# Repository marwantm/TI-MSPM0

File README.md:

# TI MSPM0 Development Board
 
A 2-layer TI MSPM0 development board, designed in KiCad by following Phil's Lab's tutorial — this time spending less effort on replicating the steps and more on understanding the engineering decisions behind each one.

## Overview
 
This board is built around the **MSPM0G3507SPTR**, an Arm Cortex-M0+ MCU from Texas Instruments. It includes USB-C power/data via a USB-UART converter, an SWD programming header, an onboard 3.3V LDO regulator, and an onboard accelerometer — a compact general-purpose MSPM0 development platform.
 
| | |
|---|---|
| **MCU** | MSPM0G3507SPTR (Arm Cortex-M0+) |
| **Peripherals** | Onboard accelerometer (I2C) |
| **Connectivity** | USB-C, USB-to-UART bridge |
| **PCB** | 2-layer |
| **Programming** | SWD header |
| **Power** | USB-C (5V → 3.3V via onboard LDO) |
| **Design Tool** | KiCad 9 |
 
## What I Learned
 
Compared to my first PCB project, I spent less time simply following the tutorial and more time understanding the engineering decisions behind each step:
 
- Creating custom schematic symbols
- Multilayer PCB concepts and layer stack-ups
- The role of signal, power, and ground layers
- PCB manufacturing basics
- Component placement strategies
- A professional PCB layout workflow
Each project is helping me strengthen both my PCB design and embedded systems fundamentals, moving closer to making these design decisions independently.
 
## Gallery
 
| Schematic | PCB Top | PCB Bottom |
|---|---|---|
|  |  |  |
 
| 3D Front | 3D Back |
|---|---|
|  |  |
 
## Repository Structure
 
```
TI-MSPM0/
├── README.md
├── Images/              # Renders and layer screenshots
├── Hardware/            # Manufacturing-ready outputs
│   ├── TI MSPM0_Schematic.pdf
│   ├── TI MSPM0_PCB.pdf
│   ├── BOM.csv
│   └── Gerbers.zip
└── Source Files/        # Full KiCad project (editable source)
```
 
## Credit
 
Built by following [Phil's Lab](https://www.youtube.com/@PhilsLab)'s TI MSPM0 development board tutorial. This project is a learning exercise, not an original design — full credit for the schematic architecture and design decisions goes to Phil's Lab's tutorial series.
 
## Author
 
**Marwan Tamer**
Electrical Power Engineering student, building toward Embedded Systems Engineering
[LinkedIn](https://www.linkedin.com/in/-marwan-tamer)

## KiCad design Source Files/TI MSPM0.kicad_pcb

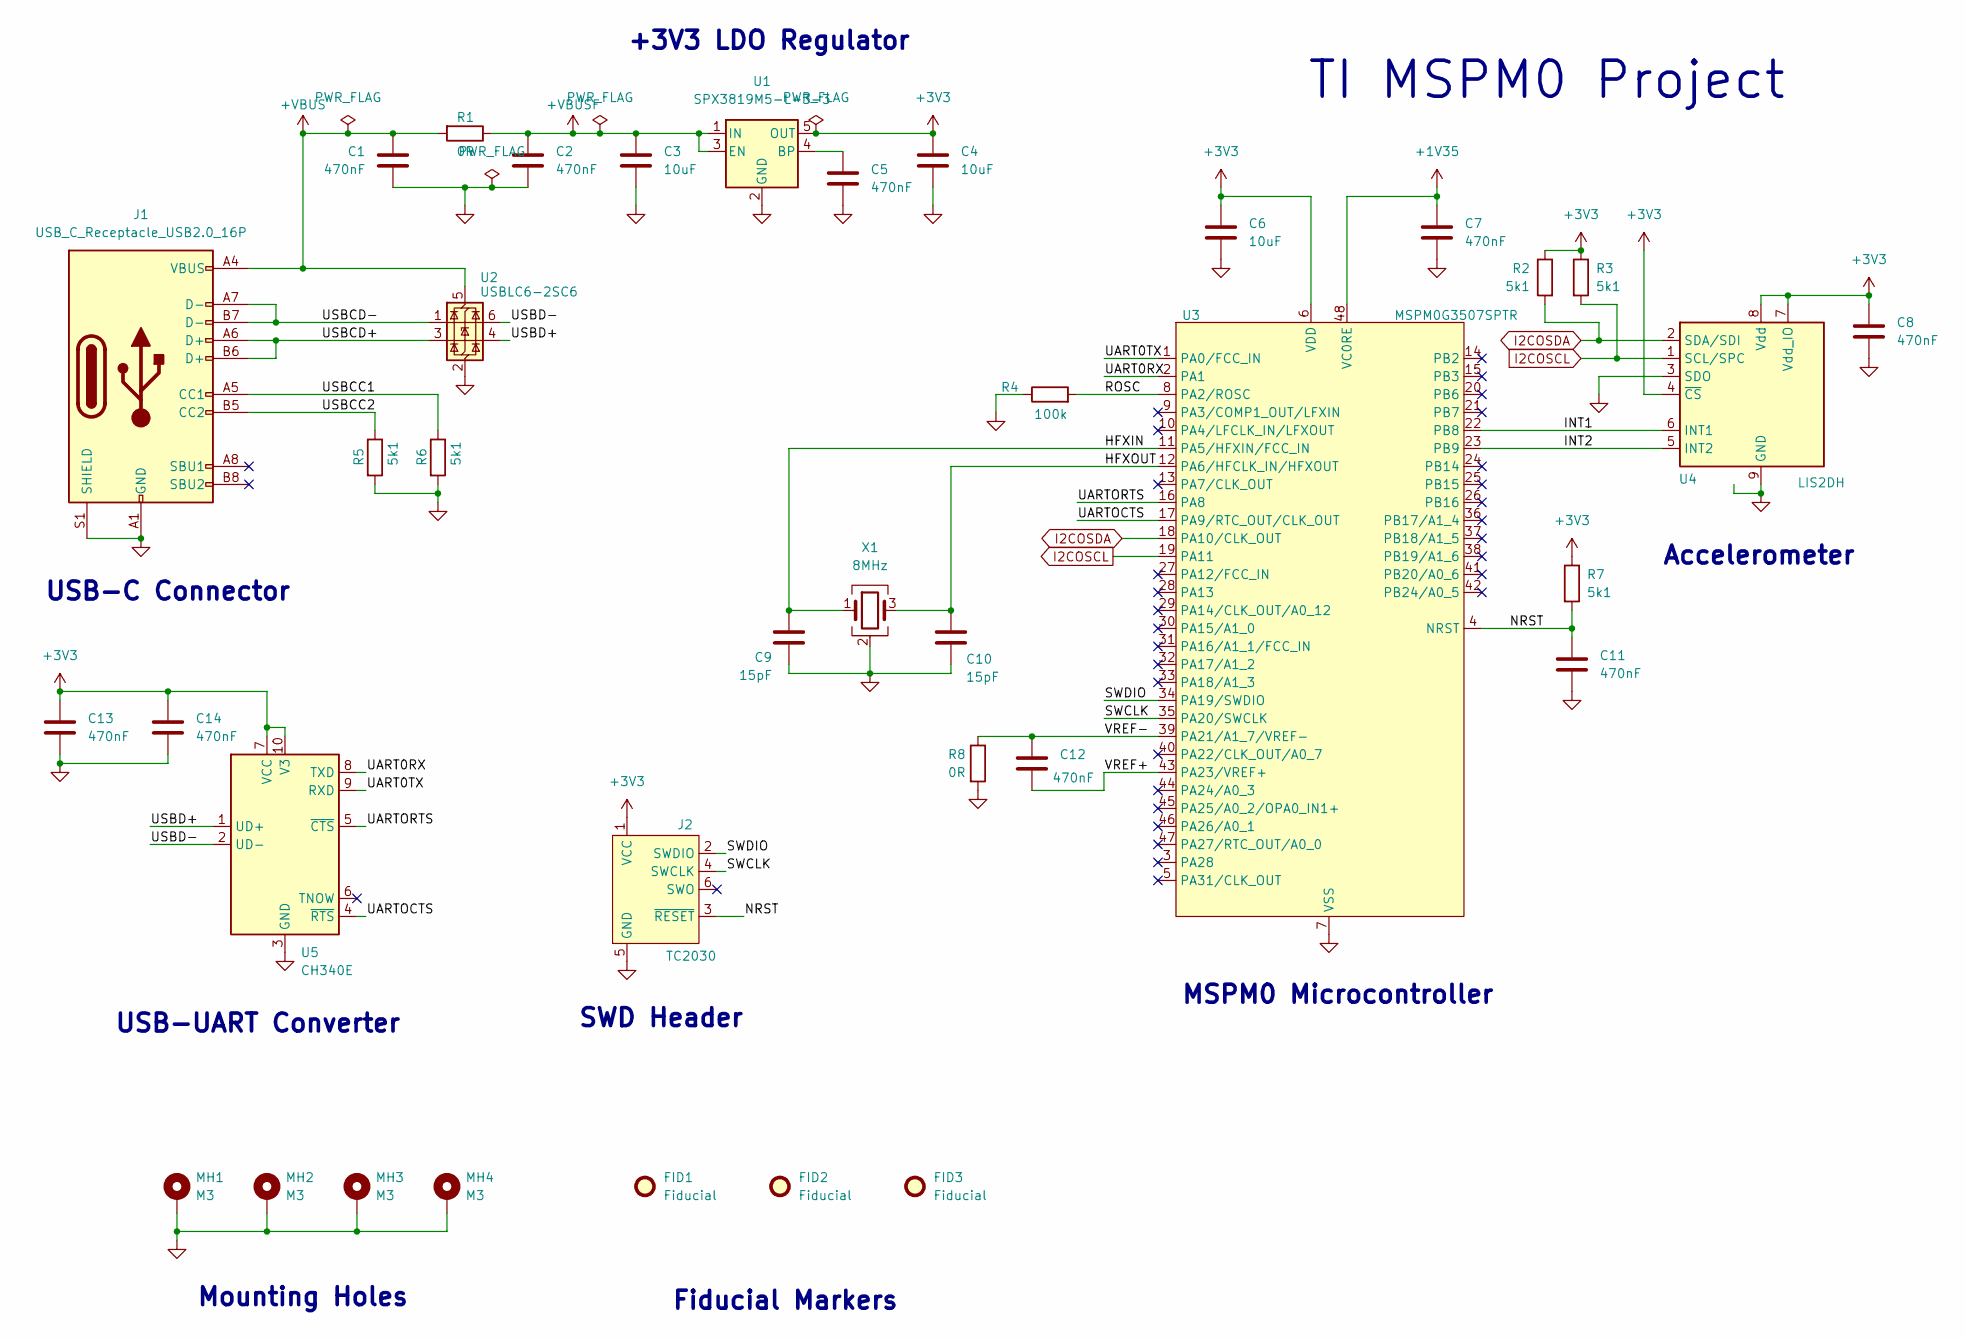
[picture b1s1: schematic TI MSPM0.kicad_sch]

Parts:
C1, C2, C5, C7, C8, C11, C12, C13, C14: 470nF; C_0603_1608Metric
C3, C4, C6: 10uF; C_0805_2012Metric
C9, C10: 15pF; C_0603_1608Metric
FID1, FID2, FID3: Fiducial; Fiducial_1mm_Mask2mm
J1: USB_C_Receptacle_USB2.0_16P; USB_C_Receptacle_GCT_USB4105-xx-A_16P_TopMnt_Horizontal
J2: TC2030; Tag-Connect_TC2030-IDC-FP_2x03_P1.27mm_Vertical
MH1, MH2, MH3, MH4: M3; MountingHole_3.2mm_M3_Pad_Via
R1, R8: 0R; R_0603_1608Metric
R2, R3, R5, R6, R7: 5k1; R_0603_1608Metric
R4: 100k; R_0603_1608Metric
U1: SPX3819M5-L-3-3; SOT-23-5
U2: USBLC6-2SC6; SOT-23-6
U3: MSPM0G3507SPTR; LQFP-48_7x7mm_P0.5mm
U4: LIS2DH; LGA-14_2x2mm_P0.35mm_LayoutBorder3x4y
U5: CH340E; MSOP-10_3x3mm_P0.5mm
X1: 8MHz; Crystal_SMD_3225-4Pin_3.2x2.5mm

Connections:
+1V35: C7.1, U3.48 (VC0RE)
+3V3: C4.1, C6.1, C8.1, C13.1, C14.1, J2.1 (VCC), R2.1, R3.1, R7.1, U1.5 (OUT), U3.6 (VDD), U4.4 (~CS), U4.7 (Vdd_IO), U4.8 (Vdd), U5.7 (VCC), U5.10 (V3)
+VBUS: C1.1, J1.A4 (VBUS), J1.A9 (VBUS), J1.B4 (VBUS), J1.B9 (VBUS), R1.2, U2.5 (VBUS)
+VBUSF: C2.1, C3.1, R1.1, U1.1 (IN), U1.3 (EN)
/HFXIN: C9.1, U3.11 (PA5/HFXIN/FCC_IN), X1.1
/HFXOUT: C10.1, U3.12 (PA6/HFCLK_IN/HFXOUT), X1.3
/INT1: U3.22 (PB8), U4.6 (INT1)
/INT2: U3.23 (PB9), U4.5 (INT2)
/NRST: C11.1, J2.3 (~RESET), R7.2, U3.4 (NRST)
/ROSC: R4.2, U3.8 (PA2/ROSC)
/SWCLK: J2.4 (SWCLK), U3.35 (PA20/SWCLK)
/SWDIO: J2.2 (SWDIO), U3.34 (PA19/SWDIO)
/UART0RX: U3.2 (PA1), U5.8 (TXD)
/UART0TX: U3.1 (PA0/FCC_IN), U5.9 (RXD)
/UARTOCTS: U3.17 (PA9/RTC_OUT/CLK_OUT), U5.4 (~RTS)
/UARTORTS: U3.16 (PA8), U5.5 (~CTS)
/USBCC1: J1.A5 (CC1), R6.1
/USBCC2: J1.B5 (CC2), R5.1
/USBCD+: J1.A6 (D+), J1.B6 (D+), U2.3 (I/O2)
/USBCD-: J1.A7 (D-), J1.B7 (D-), U2.1 (I/O1)
/USBD+: U2.4 (I/O2), U5.1 (UD+)
/USBD-: U2.6 (I/O1), U5.2 (UD-)
/VREF+: C12.2, U3.43 (PA23/VREF+)
/VREF-: C12.1, R8.1, U3.39 (PA21/A1_7/VREF-)
GND: C1.2, C2.2, C3.2, C4.2, C5.2, C6.2, C7.2, C8.2, C9.2, C10.2, C11.2, C13.2, C14.2, J1.A1 (GND), J1.A12 (GND), J1.B1 (GND), J1.B12 (GND), J1.S1 (SHIELD), J2.5 (GND), MH1.1, MH2.1, MH3.1, MH4.1, R4.1, R5.2, R6.2, R8.2, U1.2 (GND), U2.2 (GND), U3.7 (VSS), U4.3 (SDO), U4.9 (GND), U4.10 (GND), U4.11 (GND), U4.12 (GND), U4.13 (GND), U4.14 (GND), U5.3 (GND), X1.2 (G), X1.4 (G)
I2COSCL: R3.2, U3.19 (PA11), U4.1 (SCL/SPC)
I2COSDA: R2.2, U3.18 (PA10/CLK_OUT), U4.2 (SDA/SDI)
unnamed: C5.1, U1.4 (BP)

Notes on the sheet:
Fiducial Markers
TI MSPM0 Project
USB-UART Converter
Mounting Holes
Accelerometer
SWD Header
USB-C Connector
MSPM0 Microcontroller
+3V3 LDO Regulator

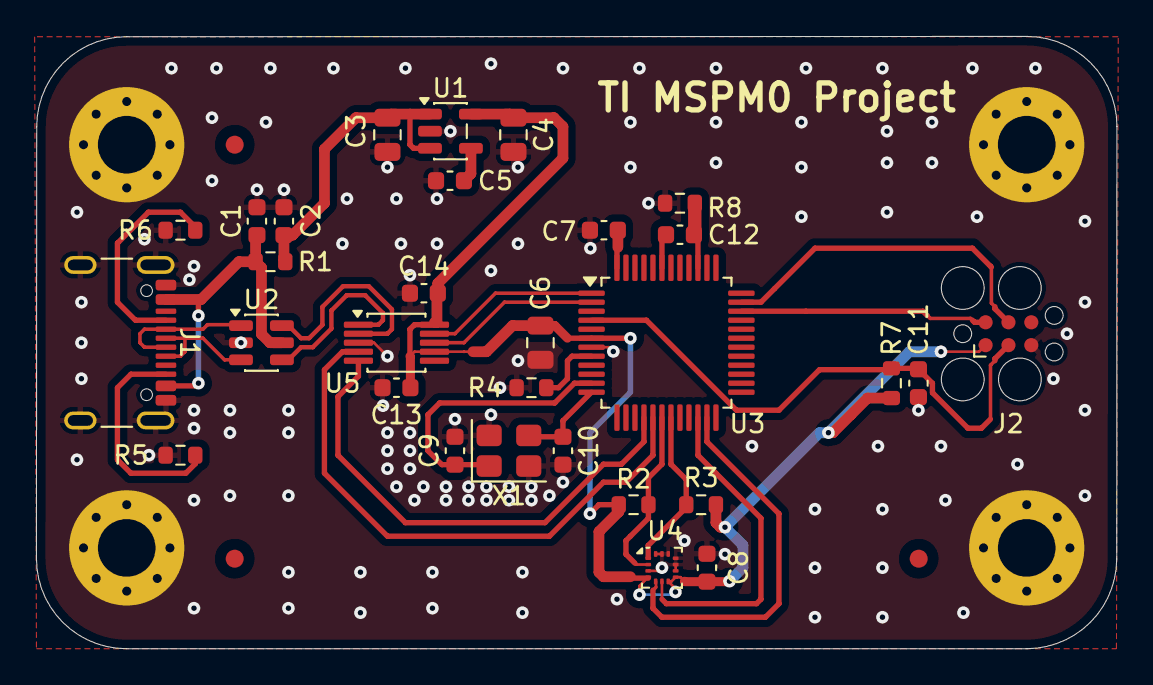
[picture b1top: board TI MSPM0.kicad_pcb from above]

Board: 2 copper layers, 60.0 x 34.0 mm, 37 parts (0 on the bottom side), 28 nets.

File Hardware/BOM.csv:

"Reference","Qty","Value","DNP","Exclude from BOM","Exclude from Board","Footprint","Datasheet"
"C1,C2,C5,C7,C8,C11,C12,C13,C14","9","470nF","","","","Capacitor_SMD:C_0603_1608Metric","~"
"C3,C4,C6","3","10uF","","","","Capacitor_SMD:C_0805_2012Metric","~"
"C9,C10","2","15pF","","","","Capacitor_SMD:C_0603_1608Metric","~"
"FID1,FID2,FID3","3","Fiducial","","Excluded from BOM","","Fiducial:Fiducial_1mm_Mask2mm","~"
"J1","1","USB_C_Receptacle_USB2.0_16P","","","","Connector_USB:USB_C_Receptacle_GCT_USB4105-xx-A_16P_TopMnt_Horizontal","https://www.usb.org/sites/default/files/documents/usb_type-c.zip"
"J2","1","TC2030","","Excluded from BOM","","Connector:Tag-Connect_TC2030-IDC-FP_2x03_P1.27mm_Vertical","https://www.tag-connect.com/wp-content/uploads/bsk-pdf-manag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"
"MH1,MH2,MH3,MH4","4","M3","","Excluded from BOM","","MountingHole:MountingHole_3.2mm_M3_Pad_Via","~"
"R1,R8","2","0R","","","","Resistor_SMD:R_0603_1608Metric","~"
"R2,R3,R5,R6,R7","5","5k1","","","","Resistor_SMD:R_0603_1608Metric","~"
"R4","1","100k","","","","Resistor_SMD:R_0603_1608Metric","~"
"U1","1","SPX3819M5-L-3-3","","","","Package_TO_SOT_SMD:SOT-23-5","https://www.exar.com/content/document.ashx?id=22106&language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"
"U2","1","USBLC6-2SC6","","","","Package_TO_SOT_SMD:SOT-23-6","https://www.st.com/resource/en/datasheet/usblc6-2.pdf"
"U3","1","MSPM0G3507SPTR","","","","Package_QFP:LQFP-48_7x7mm_P0.5mm",""
"U4","1","LIS2DH","","","","Package_LGA:LGA-14_2x2mm_P0.35mm_LayoutBorder3x4y","http://www.st.com/web/en/resource/technical/document/datashe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"
"U5","1","CH340E","","","","Package_SO:MSOP-10_3x3mm_P0.5mm","https://www.mpja.com/download/35227cpdata.pdf"
"X1","1","8MHz","","","","Crystal:Crystal_SMD_3225-4Pin_3.2x2.5mm","~"
